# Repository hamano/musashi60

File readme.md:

# Musashi60 - Open Hardware Keyboard

## Overview

Musashi60 is open-hardware splitted keyboard.

* Keys: 60
* Layout: Ergonomic column-staggered
* All parts are available to procured or make yourself. see [parts](#parts-list).
* Keyboard Maintainer: [HAMANO Tsukasa](https://github.com/hamano)
* Hardware Supported: The PCBs, controllers supported
* Hardware Availability: Links to where you can find this hardware

Make example for this keyboard (after setting up your build environment):

    make musashi60:default

See the [build environment setup](https://docs.qmk.fm/#/getting_started_build_tools) and the [make instructions](https://docs.qmk.fm/#/getting_started_make_guide) for more information. Brand new to QMK? Start with our [Complete Newbs Guide](https://docs.qmk.fm/#/newbs).

## Gallery

## Parts list

- RP2024
- PCB
- case
- plate
- screw

## Build guide

Comming soon...

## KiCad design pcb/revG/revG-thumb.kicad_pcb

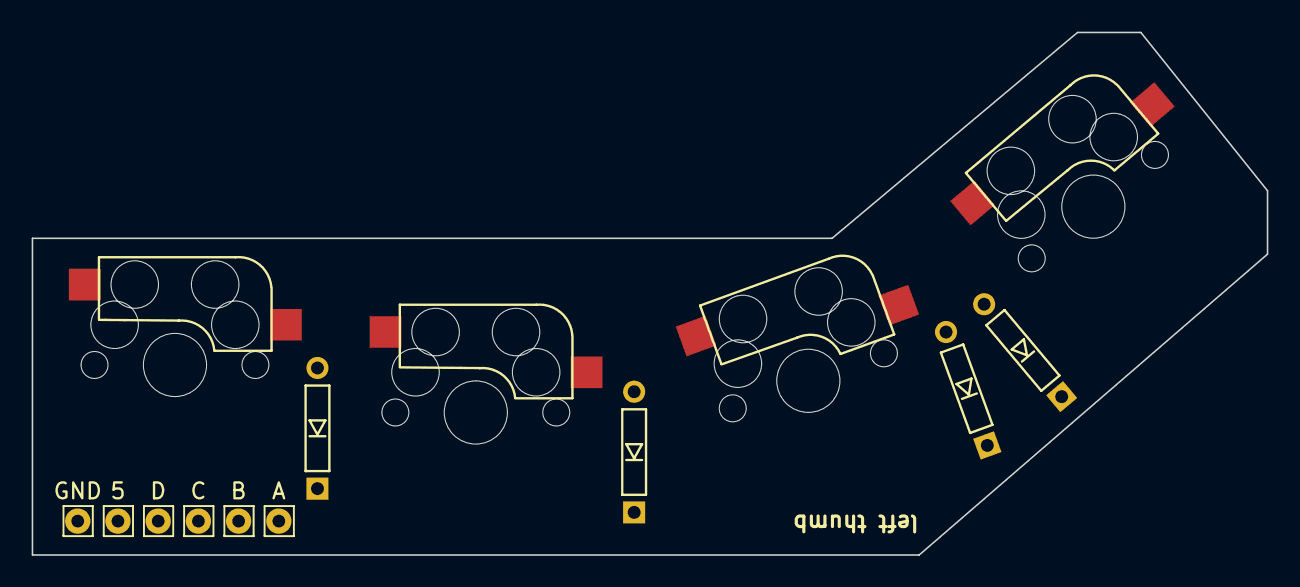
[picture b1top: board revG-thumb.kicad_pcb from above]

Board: 2 copper layers, 78.0 x 33.0 mm, 14 parts (0 on the bottom side), 9 nets, no tracks yet.

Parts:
D_LA5: D_A5; D_TH_Reversible
D_LB5: D_B5; D_TH_Reversible
D_LC5: D_C5; D_TH_Reversible
D_LD5: D_D5; D_TH_Reversible
H_L5: 5; Pin_D0.8mm
H_LA1: A; Pin_D0.8mm
H_LB1: B; Pin_D0.8mm
H_LC1: C; Pin_D0.8mm
H_LD5: D; Pin_D0.8mm
H_LGND1: GND; Pin_D0.8mm
SW_LA5: SW_PUSH-foostan; CherryMX_Hotswap_Reversible
SW_LB5: SW_PUSH-foostan; CherryMX_Hotswap_Reversible
SW_LC5: SW_PUSH-foostan; CherryMX_Hotswap_Reversible
SW_LD5: SW_PUSH-foostan; CherryMX_Hotswap_Reversible

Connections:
unnamed: D_LA5.1, D_LB5.1, D_LC5.1, D_LD5.1, H_L5.1
unnamed: D_LA5.2, SW_LA5.1
unnamed: D_LB5.2, SW_LB5.1
unnamed: D_LC5.2, SW_LC5.1
unnamed: D_LD5.2, SW_LD5.1
unnamed: H_LA1.1, SW_LA5.2
unnamed: H_LB1.1, SW_LB5.2
unnamed: H_LC1.1, SW_LC5.2
unnamed: H_LD5.1, SW_LD5.2

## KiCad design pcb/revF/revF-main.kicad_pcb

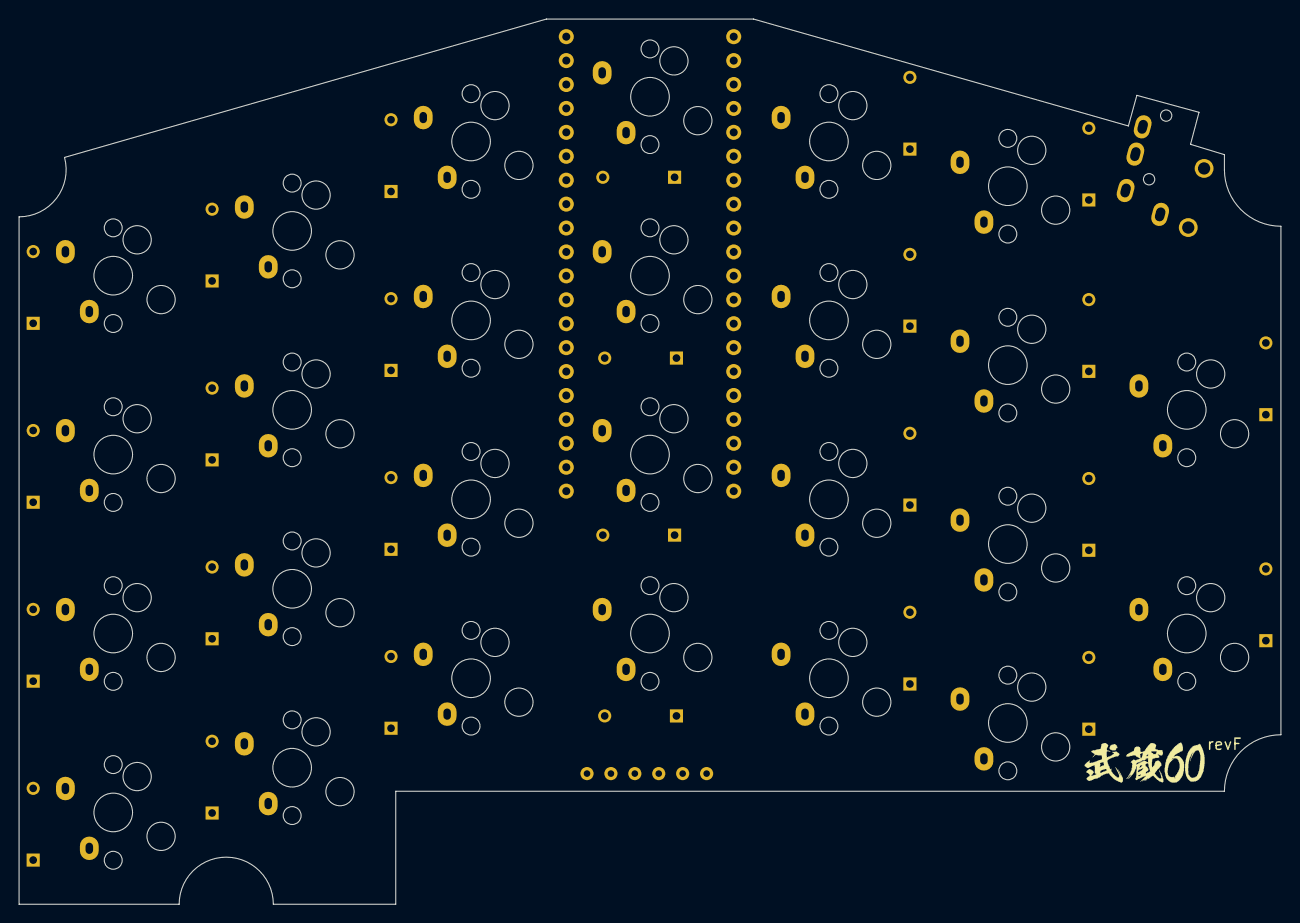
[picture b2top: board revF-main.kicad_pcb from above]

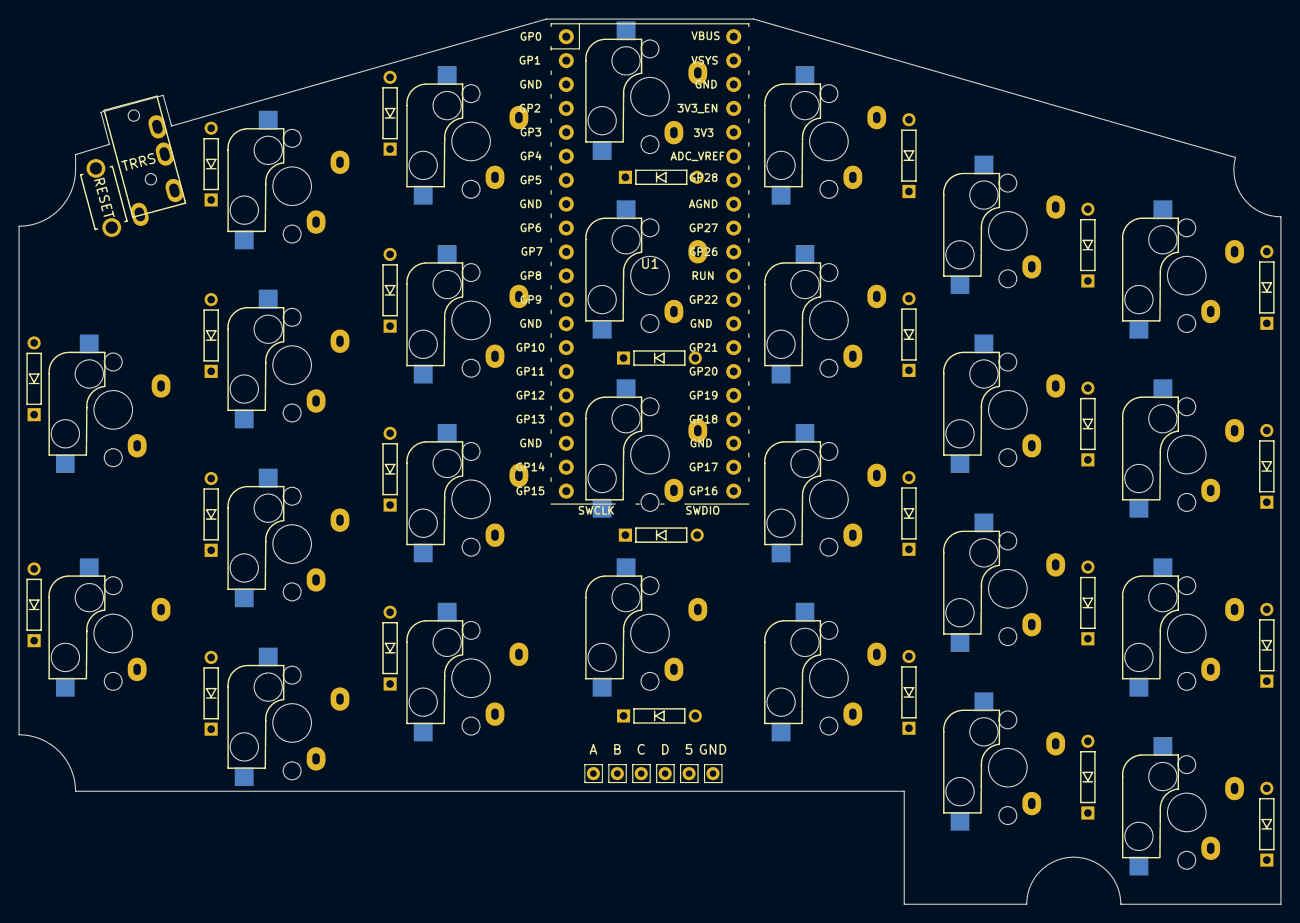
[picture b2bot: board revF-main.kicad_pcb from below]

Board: 2 copper layers, 134.0 x 94.0 mm, 61 parts (35 on the bottom side), 42 nets, no tracks yet.

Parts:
D_A2, D_A3: D; D_TH
D_B1, D_B2, D_B3, D_B4: D; D_TH
D_C1, D_C2, D_C3, D_C4: D; D_TH
D_D1, D_D2, D_D3, D_D4: D; D_TH
D_E1, D_E2, D_E3, D_E4: D; D_TH
D_F1, D_F2, D_F3, D_F4: D; D_TH
D_G1, D_G2, D_G3, D_G4: D; D_TH
H_5: 5; Pin_D0.7mm
H_A1: A; Pin_D0.7mm
H_B1: B; Pin_D0.7mm
H_C1: C; Pin_D0.7mm
H_D1: D; Pin_D0.7mm
H_GND1: GND; Pin_D0.7mm
J1: MJ-4PP-9
SW_A2, SW_A3: SW_PUSH; CherryMX_Direct_Hotswap
SW_B1, SW_B2, SW_B3, SW_B4: SW_PUSH; CherryMX_Direct_Hotswap
SW_C1, SW_C2, SW_C3, SW_C4: SW_PUSH; CherryMX_Direct_Hotswap
SW_D1, SW_D2, SW_D3, SW_D4: SW_PUSH; CherryMX_Direct_Hotswap
SW_E1, SW_E2, SW_E3, SW_E4: SW_PUSH; CherryMX_Direct_Hotswap
SW_F1, SW_F2, SW_F3, SW_F4: SW_PUSH; CherryMX_Direct_Hotswap
SW_G1, SW_G2, SW_G3, SW_G4: SW_PUSH; CherryMX_Direct_Hotswap
SW_RST1: SW_DIP_x01; ResetSW
U1: Pico; RPi_Pico_TH

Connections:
GND: H_GND1.1, J1.C, SW_RST1.1, U1.3, U1.8, U1.13, U1.18, U1.23, U1.28, U1.38
unnamed: D_A2.2, SW_A2.2
unnamed: D_A3.2, SW_A3.2
unnamed: D_B1.2, SW_B1.2
unnamed: D_B2.2, SW_B2.2
unnamed: D_B3.2, SW_B3.2
unnamed: D_B4.2, SW_B4.2
unnamed: D_C1.2, SW_C1.2
unnamed: D_C2.2, SW_C2.2
unnamed: D_C3.2, SW_C3.2
unnamed: D_C4.2, SW_C4.2
unnamed: D_D1.2, SW_D1.2
unnamed: D_D2.2, SW_D2.2
unnamed: D_D3.2, SW_D3.2
unnamed: D_D4.2, SW_D4.2
unnamed: D_E1.2, SW_E1.2
unnamed: D_E2.2, SW_E2.2
unnamed: D_E3.2, SW_E3.2
unnamed: D_E4.2, SW_E4.2
unnamed: D_F1.2, SW_F1.2
unnamed: D_F2.2, SW_F2.2
unnamed: D_F3.2, SW_F3.2
unnamed: D_F4.2, SW_F4.2
unnamed: D_G1.2, SW_G1.2
unnamed: D_G2.2, SW_G2.2
unnamed: D_G3.2, SW_G3.2
unnamed: D_G4.2, SW_G4.2
RUN: SW_RST1.2, U1.30
colA: H_A1.1, U1.21
colB: H_B1.1, U1.22
colC: H_C1.1, U1.24
colD: H_D1.1, U1.25
colE: SW_E4.1, U1.26
colF: SW_F4.1, U1.27
colG: SW_G4.1, U1.29
data: J1.B, U1.4
hand: J1.D, U1.5, U1.39
row1: D_B1.1, D_C1.1, D_D1.1, D_E1.1, D_F1.1, D_G1.1, U1.14
row2: D_A2.1, D_B2.1, D_C2.1, D_D2.1, D_E2.1, D_F2.1, D_G2.1, U1.15
row3: D_A3.1, D_B3.1, D_C3.1, D_D3.1, D_E3.1, D_F3.1, D_G3.1, U1.16
row4: D_B4.1, D_C4.1, D_D4.1, D_E4.1, D_F4.1, D_G4.1, U1.17
row5: H_5.1, U1.19

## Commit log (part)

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2020-12-08 update keymap
2020-12-11 Revert "remove musashi60.sch"
    This reverts commit e95140cd4166689b95f370a70f5812e26694df12.
2020-12-11 update pcb
2020-12-11 add silk logo
2021-01-05 update switch footprint
2021-01-12 add silk footprint
2021-01-12 change TAPPING_TERM
2021-01-12 change MANUFACTURER
2021-01-12 update circut
2021-01-19 update for rev7 pcb
2021-01-19 update for rev7 key layout
2021-01-19 update keymap for rev7
2021-02-04 set CONSOLE_ENABLE = no
2021-02-04 change keylayout
2021-02-04 add musashi50 silk
2021-02-04 add local components
2021-02-04 rename footprint
2021-02-04 add J08K footprint
2021-02-05 add pointing device
2021-02-05 change product id
2021-02-05 update circut for rev8
2021-02-05 update pcb for rev8
2021-02-05 happy new year
2021-02-05 add wheel mode
2021-02-05 PCBの微調整
2021-02-09 change matrix
2021-02-09 change layout
2021-02-09 change keymap
2021-02-12 add custom transport.c
2021-02-12 fix trackpoint
2021-02-12 add trackpoint cap model
2021-02-12 add trackpoint stl
2021-02-13 add .editorconfig
2021-02-13 update custom transport for trackpoint
2021-02-13 add trackpoint functions
2021-02-13 renamed
2021-02-13 remove unused code
2021-02-15 rename pcb
2021-02-15 rename sch
2021-02-15 add rev8 snapshot
2021-03-19 undef RETRO_TAPPING
2021-03-19 add js symbol
2021-03-19 update J08K footprint
2021-03-19 update footprint
2021-03-19 remove musashi50-rev8.sch
2021-03-22 adjsut joystick axis
2021-03-22 cleanup
2021-03-22 update rev9
2021-03-23 add joystick calibration
2021-03-23 add joystick calibration key
2021-03-23 add pcb rev9
2021-05-01 add eucalyn layout
2021-05-01 use Joycon_Stick_Short
2021-05-01 add Joycon_Stick_Short footprint
2021-05-01 add Joycon_Stick footprint
2021-05-01 remove test pin
2021-05-31 update layout
2021-05-31 add nojs flag
2021-05-31 update scheme
2021-05-31 disable pointing device
2021-06-10 add musashi60-revA-wired.kicad_pcb
2021-06-10 update sch
2021-06-21 update sw footprint
2021-06-21 update for revB
2021-06-21 remove js cap
2021-07-05 remove rev8 pcb
2021-07-05 add revB-case-v6
2021-07-05 remove rev9 pcb
2021-07-05 add last key
2021-07-05 disable custom transport
2021-07-05 add revB firmware
2021-07-05 add revB case
2021-07-08 add revB wired pcb
2021-07-08 add revB sch
2021-07-08 add revC sch
2021-07-08 add revC pcb
2021-07-16 add new promicro footprint
2021-07-16 update for revC
2021-07-16 add revC wired pcb
2021-07-16 add revB/rules.mk
2021-07-16 add revC config
2021-07-16 update revC layout
2021-07-16 update key layout
2021-07-16 use revC
2021-07-16 add revC/rules.mk
2021-07-16 add revC case
2021-07-16 add OLED footprint
2021-07-16 add revD pcb
2021-07-30 update revD pcb
2021-07-30 update revD scheme
2021-07-30 add jumper footprint
2021-08-19 update scheme for revD
2021-08-19 add OLED_Reversible_Jumper
2021-08-19 add wired pcb for revD
2021-08-19 add case for revD
2021-08-19 add footprint
2021-09-03 update revB
2021-09-03 add .gitignore
2021-09-03 add FUNDING.yml
2021-09-04 add revD tilt
2021-09-04 rename dir
2021-09-04 add revB plate
2021-09-04 add revD plate
2021-09-04 add revD case
2021-09-04 rename revC case
2021-09-04 rename revB case
2021-09-04 rename revD case
2021-09-04 add revD svg
2021-09-04 update gallery image
2021-09-04 add resetsw footprint
2021-09-04 update logo
2021-09-04 remove old image
2021-11-24 add new case
2021-11-26 rotate keyhole
2021-11-26 add hole
2021-11-26 add rpi pico symbol
2021-11-26 add keyswitch foot print
2021-11-28 rename files
2021-11-28 update add pico footprint
2021-11-28 add D_TH_Reversible.kicad_mod
2021-11-28 add pcb/local.pretty/Pin_D0.7mm.kicad_mod
2021-11-28 add update promicro footprint
2021-11-28 update diode footprint
2021-11-28 update key switch footprint
2021-12-01 add pico footprint
2021-12-01 add 5pin fpc footprint
2021-12-01 add reversible reset switch footprint footprint
2021-12-01 change dirs
2021-12-01 add sw footprint
2021-12-01 fix pico symbol
2021-12-01 update finger case
2021-12-01 update pico footprint
2021-12-01 update resetsw footprint
2021-12-01 update mouse bite footprint
2021-12-02 remove old pcb
2021-12-02 dir change
2021-12-02 add MJ-4PP-9 footprint
2021-12-02 remove olf scheme
2021-12-02 add rescue.lib
2021-12-02 add revA pcb
2021-12-02 rename revB firmware
2021-12-02 rename revD firmware
2021-12-06 add qmk/revE
2021-12-06 use qmk/revE
2021-12-06 add revE pcb
2021-12-06 add revE right pcb
2021-12-06 add thumb pcb
2021-12-06 add thumb net
2021-12-07 add revB pcb
2021-12-10 change clearance of joint
2021-12-10 update case
2021-12-10 add kmk key layout
2021-12-10 add kmk code
2021-12-24 set onboard led high
2021-12-24 add pico symbol
2021-12-24 update revE case
2021-12-24 update revE plate
2021-12-30 add revE thumb case
2021-12-30 add revA pro file
2021-12-30 add revB pro file
2021-12-30 add revF sch
2021-12-30 add revF pcb
2022-01-14 add revE.pro
2022-01-14 add revE.lib
2022-01-14 add revF-main.pro
2022-01-14 add revF-main-left.pro
2022-01-14 add revF-main-left.kicad_pcb
2022-02-08 update thumb case
2022-02-08 update thumb case stl
2022-02-08 update stl
2022-02-08 add revF/thumb.scad
2022-02-18 add revF common
2022-02-18 update revF thumb
2022-02-18 update revF finger
2022-02-20 update revF finger case
2022-02-20 update revF thumb case
2022-02-20 add Makefile
2022-02-20 add revF case and plate
2022-02-22 change joint clealance
2022-04-21 update thumb
2022-04-23 add musashi60 symbol
2022-04-23 update revE schema
2022-04-23 add revF.pro
2022-04-23 add revF-thumb.sch
2022-04-23 add revF-thumb.net
2022-04-23 add revF-thumb.kicad_pcb
2022-04-23 add revF-thumb-wired.kicad_pcb
2022-04-23 remove unused symbol
2022-04-24 update rev8 pcb
2022-04-25 add revF-thumb-reversible.sch
2022-04-25 add revF-thumb-reversible.net
2022-04-25 add revF-thumb-reversible.kicad_pcb
2022-04-25 add revF-thumb-reversible-wired.kicad_pcb
2022-05-06 update revF stl
2022-05-07 update finger
2022-05-11 add revF config
2022-05-11 add revF rules
2022-05-11 Off pico led
2022-05-11 switch to revF
2022-05-11 remove MCU_RaspberryPi_and_Boards.dcm
2022-05-11 remove MCU_RaspberryPi_and_Boards.lib
2022-05-11 add musashi60-symbol.dcm
2022-05-11 add old pcb resources
2022-06-06 copy from revF
2022-06-19 update revG thumb
2022-06-19 add key hole cls
2022-06-19 add finger.scad
2022-06-19 add finger_case.scad
2022-06-19 finger_plate.scad
2022-06-19 update Makefile
2022-06-19 add cls to switch hole
2022-07-06 more cls
2022-07-24 update revG finger
2022-07-25 add revG.pro
2022-07-25 add revG-thumb.sch
2022-07-25 add revG-thumb.net
2022-07-26 add revG-thumb-wired.kicad_pcb
2022-08-04 change cls
2022-08-04 change cable hole
2022-08-04 add thumb stl
2022-08-04 add revG firmware
2022-08-05 remove deprecated option
2022-08-05 disable debug
2022-10-02 renamed revE
2022-10-02 update main case
2022-10-07 add keycap.scad
2022-10-15 add joint param
2022-10-15 change trrs hole
2022-10-15 add unit_case.scad
2024-12-19 rename
2024-12-19 add photo
